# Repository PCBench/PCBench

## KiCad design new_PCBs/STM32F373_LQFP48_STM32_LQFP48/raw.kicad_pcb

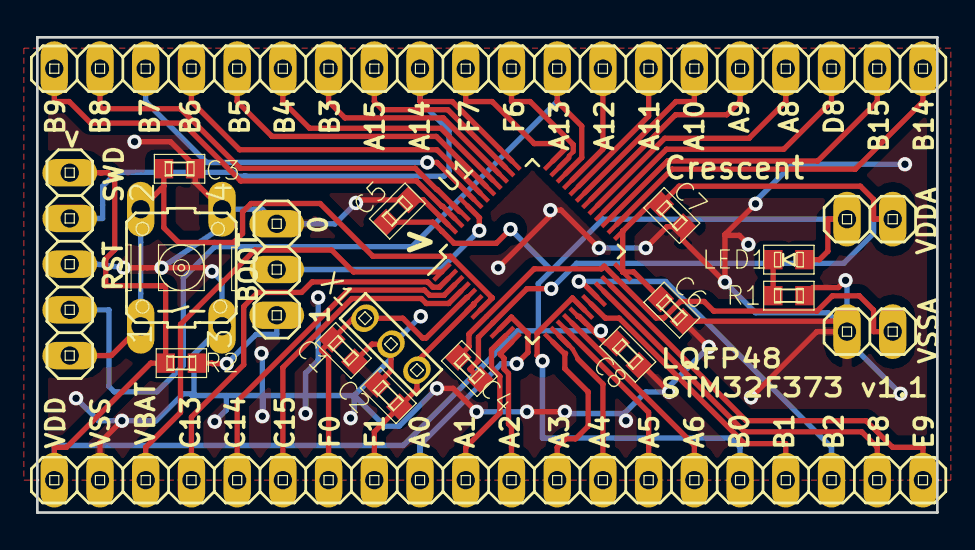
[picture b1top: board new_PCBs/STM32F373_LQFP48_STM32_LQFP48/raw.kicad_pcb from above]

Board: 2 copper layers, 50.0 x 26.4 mm, 20 parts (0 on the bottom side), 46 nets.

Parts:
C1, C2, C3, C4, C5, C6, C7, C8: CAPACITOR1608; generic-SMD1608
JP1: PINHD-1X5; pinhead-1X05
JP2: PINHD-1X3; pinhead-1X03
JP3, JP5: PINHD-1X2; pinhead-1X02
JP4, JP6: PINHD-1X20; pinhead-1X20
LED1: LED1608; generic-LED1608
R1, R2: RESISTOR1608; generic-SMD1608
S1: 10-XX; switch-omron-B3F-10XX
U1: STM32F100C8; LQFP-48_7x7mm_Pitch0.5mm
X1: CRYSTAL_SMD; pinhead-1X03

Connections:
BOOT: JP2.2, U1.44
NRST: C3.1, JP1.5, S1.1, S1.2, U1.7
unnamed: JP2.1, R2.2
unnamed: LED1.K, R1.1
OSCI: C1.1, JP4.7, U1.5, X1.1
OSCO: C2.1, JP4.8, U1.6, X1.2
PA0: JP4.9, U1.10
PA1: JP4.10, U1.11
PA2: JP4.11, U1.12
PA3: JP4.12, U1.13
PA4: JP4.13, U1.14
PA5: JP4.14, U1.15
PA6: JP4.15, U1.16
PA8: JP6.17, U1.29
PA9: JP6.16, U1.30
PA10: JP6.15, U1.31
PA11: JP6.14, U1.32
PA12: JP6.13, U1.33
PA13: JP1.4, JP6.12, U1.34
PA14: JP1.2, JP6.9, U1.37
PA15: JP6.8, U1.38
PB0: JP4.16, U1.18
PB1: JP4.17, U1.19
PB2: JP4.18, U1.20
PB3: JP6.7, U1.39
PB4: JP6.6, U1.40
PB5: JP6.5, U1.41
PB6: JP6.4, U1.42
PB7: JP6.3, U1.43
PB8: JP6.2, U1.45
PB9: JP6.1, U1.46
PB14: JP6.20, U1.26
PB15: JP6.19, U1.27
PC13: JP4.4, U1.2
PC14: JP4.5, U1.3
PC15: JP4.6, U1.4
PD8: JP6.18, U1.28
PE8: JP4.19, U1.21
PE9: JP4.20, U1.22
PF6: JP6.11, U1.35
PF7: JP6.10, U1.36
VBAT: JP4.3, U1.1
VDD: C5.1, C8.1, JP1.1, JP3.1, JP4.1, LED1.A, R2.1, U1.17, U1.48
VDDA: C4.1, C6.1, C7.1, JP3.2, U1.9, U1.24, U1.25
VSS: C1.2, C2.2, C3.2, C5.2, C6.2, C7.2, C8.2, JP1.3, JP2.3, JP4.2, JP5.1, R1.2, S1.3, S1.4, U1.47, X1.3
VSSA: C4.2, JP5.2, U1.8, U1.23

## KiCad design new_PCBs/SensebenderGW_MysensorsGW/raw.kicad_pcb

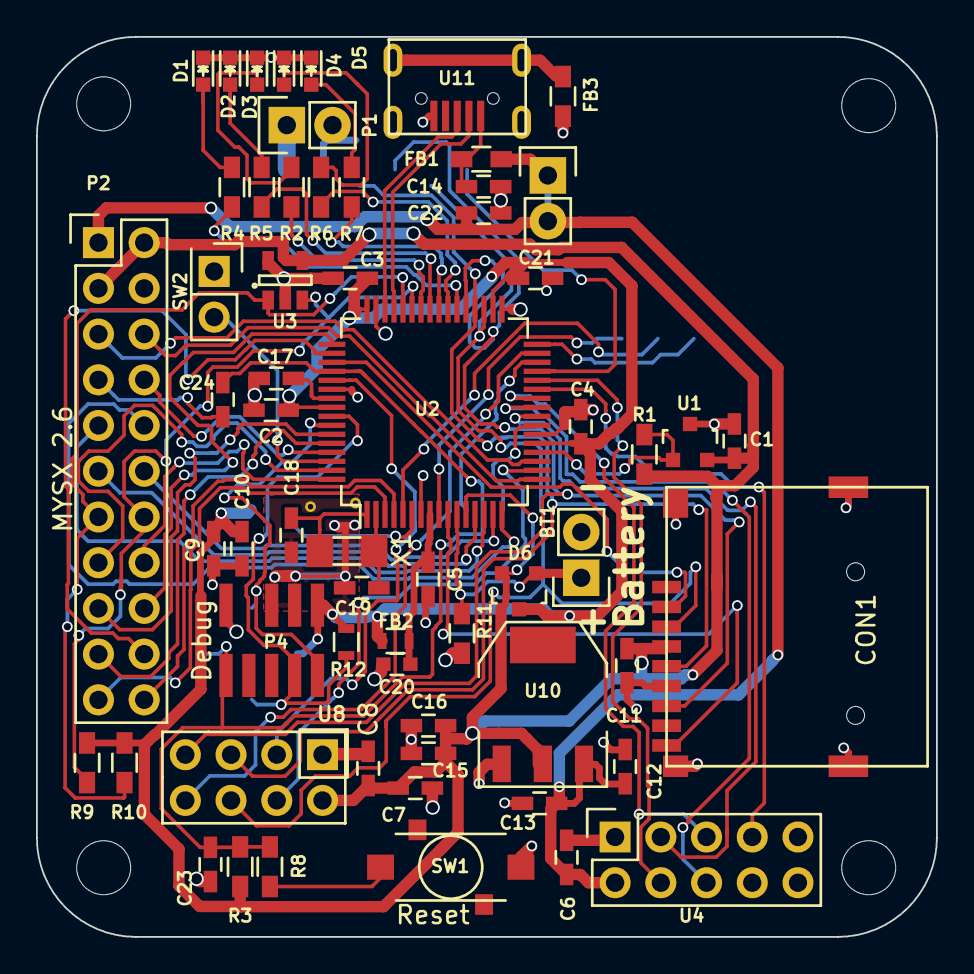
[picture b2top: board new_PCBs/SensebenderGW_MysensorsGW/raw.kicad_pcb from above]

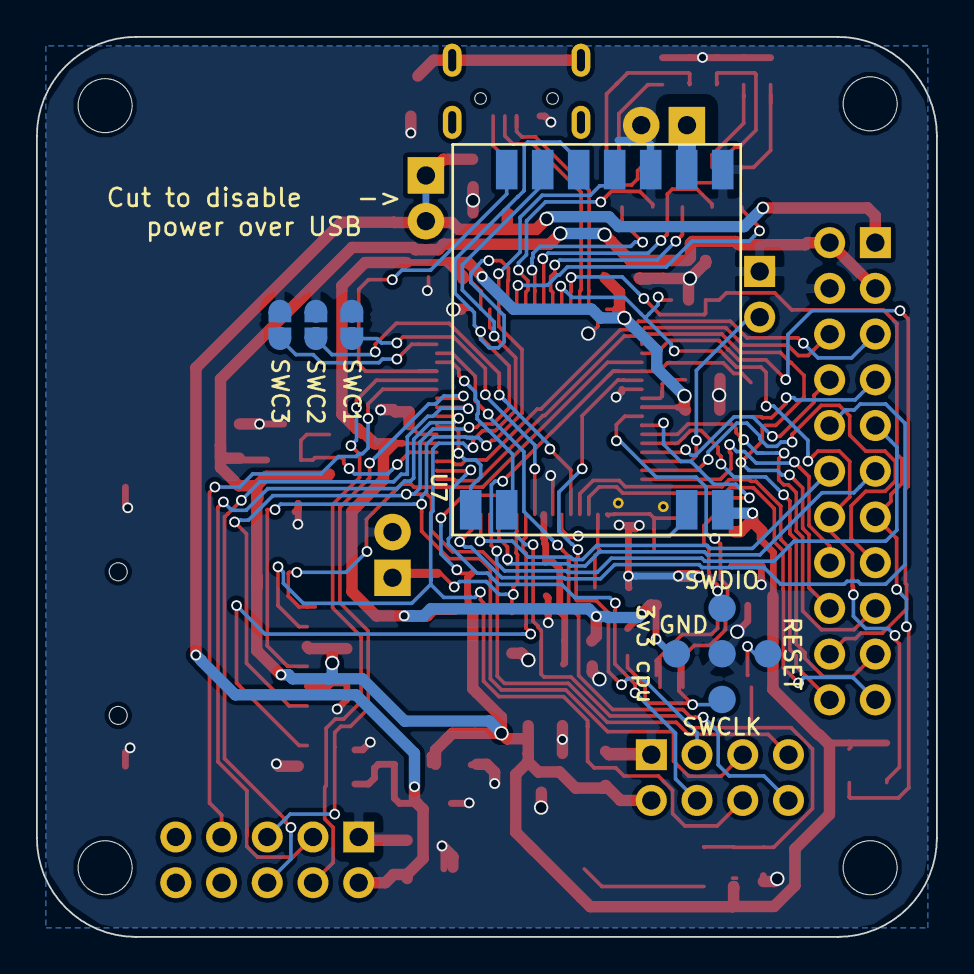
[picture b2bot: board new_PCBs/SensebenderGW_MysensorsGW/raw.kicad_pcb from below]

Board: 2 copper layers, 50.0 x 50.0 mm, 70 parts (9 on the bottom side), 68 nets.

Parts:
BT1: Battery; Pin_Header_Straight_1x02
C1, C2, C3, C4, C5, C6, C7, C10, C11, C13, C15, C17, C21, C24: 100nF; C_0603_HandSoldering
C8, C9, C12, C16: 10uF; C_0603_HandSoldering
C14, C22: 1nF; C_0603_HandSoldering
C18, C19: 4.7pF; C_0603_HandSoldering
C20: 10uF; C_0603
C23: 10nF; C_0603_HandSoldering
CON1: micro_SD_Card_SPI; MM027S020R
D1: LED_BLUE; LED-0603
D2: LED_RED; LED-0603
D3: LED_GREEN; LED-0603
D4: LED_YELLOW; LED-0603
D5: LED_ORANGE; LED-0603
D6: BAT54; SOT-23
FB1, FB3: 470R EMI; R_0603_HandSoldering
FB2: 470R EMI; R_0603
P1: ANT; Pin_Header_Straight_1x02
P2: MYSX 2.6; MYSX_2.6
P3: SWC3; 2_pin_solder_jumper_smd
P4: Debug; Cortex_M_Debug_Connector
P5: USB_PWR_DIS; Pin_Header_Straight_1x02
P6: SWC2; 2_pin_solder_jumper_smd
P7: SWC1; 2_pin_solder_jumper_smd
R1, R9, R10: 4k7; R_0603_HandSoldering
R2, R5, R6, R7: 270; R_0603_HandSoldering
R3: 100k; R_0603_HandSoldering
R4: 91; R_0603_HandSoldering
R8: 39R; R_0603_HandSoldering
R11: 1M; R_0603_HandSoldering
R12: 1K; R_0603
SW1: Reset; TS-021
SW2: SW_INCL; Pin_Header_Straight_2x01
U1: ATSHA204A; SOT-23
U2: ATSAMD21J; TQFP-64_10x10mm_Pitch0.5mm
U3: AT24CS32-STUM; SOT-23-5
U4: W5100
U7: RFM69HW; RFM69HW_SMD
U8: NRF24L01
U10: AMS1117-3.3; SOT-223
U11: MICRO-B_USB; Micro_USB
W1: SWDIO; Measurement_Point_Round-SMD-Pad_Small
W2: SWCLK; Measurement_Point_Round-SMD-Pad_Small
W3: RESET; Measurement_Point_Round-SMD-Pad_Small
W4: GND; Measurement_Point_Round-SMD-Pad_Small
W5: 3v3 cpu; Measurement_Point_Round-SMD-Pad_Small
X1: 32768hz; XTAL_3.2x1.5mm

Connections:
+3.3VP: C2.1, C3.1, C4.1, C21.1, D6.3, FB2.2, P4.1, R12.1, U2.21, U2.34, U2.48, U2.56, W5.1
+3V3: C1.1, C7.1, C8.1, C9.2, C10.2, C11.2, C15.1, C16.1, CON1.4, D6.2, P2.2, P2.3, R1.1, R3.1, R9.1, R10.1, U1.2, U2.12, U3.4, U7.8, U8.2, U10.2
+5V: C6.1, C12.1, C13.1, C22.1, FB1.1, P2.1, P5.1, P5.2, U4.2, U10.3
/A5: P2.21, U2.3
/A6: P2.22, U2.4
/BAT_DET: BT1.1, D6.1, R11.1, U2.11
/CE_NRF: U2.53, U8.3
/CS_NRF: U2.18, U8.4
/CS_RFM: U2.29, U7.15
/CS_SDCARD: CON1.2, U2.51
/D1_DFM: P2.5, U2.19
/D2_DTM: P2.6, U2.17
/D3_INT: P2.9, U2.14
/D4_INT: P2.10, U2.16
/D5_PWM: P2.11, U2.13
/D6_PWM: P2.12, U2.15
/D7_SCL: P2.13, R10.2, U2.44, U3.1
/D8_SDA: P2.14, R9.2, U2.43, U3.3
/D9_A3: P2.15, U2.63
/D10_A4: P2.16, U2.64
/D11_MOSI: P2.17, U2.59
/D12_MISO: P2.18, U2.49
/D13_SCK: P2.19, U2.60
/D14_CS: P2.20, U2.50
/D+: U2.46, U11.3
/D-: U2.45, U11.2
/INCL_SW: SW2.2, U2.62
/IRQ_NRF: U2.31, U8.8
/IRQ_RFM: U2.30, U7.2
/LED1: R4.2, U2.38
/LED2: R5.2, U2.41
/LED3: R2.2, U2.42
/LED4: R6.2, U2.39
/LED5: R7.2, U2.40
/LEGACY_ID: P2.8, U2.61
/MISO: CON1.7, U2.37, U7.13, U8.7
/MOSI: CON1.3, U2.35, U7.14, U8.6
/NET_MISO: U2.27, U4.7
/NET_MOSI: U2.25, U4.6
/NET_RST: U2.24, U4.3
/NET_SCK: U2.26, U4.5
/NET_SS: U2.28, U4.4
/RESET_RFM: U2.23, U7.1
/RFM_DIO5: U2.6, U7.7
/RST: C24.2, P2.7
/Reset: C23.1, C24.1, P4.10, R3.2, R8.1, U2.52, W3.1
/SCK: CON1.5, U2.36, U7.12, U8.5
/SDCARD_DET: CON1.9, U2.10
/SECURITY: R1.2, U1.1, U2.20
/SWC1: P7.2, U2.9
/SWC2: P6.1, U2.5
/SWC3: P3.2, U2.32
/SWCLK: P4.4, R12.2, U2.57, W2.1
/SWDIO: P4.2, U2.58, W1.1
GND: BT1.2, C1.2, C2.2, C3.2, C4.2, C5.2, C6.2, C7.2, C8.2, C9.1, C10.1, C11.1, C12.2, C13.2, C14.1, C15.2, C16.2, C17.1, C18.1, C19.1, C20.2, C21.2, C22.2, C23.2, CON1.6, CON1.10, D1.1, D2.1, D3.1, D4.1, D5.1, FB3.1, P1.2, P2.4, P3.1, P4.3, P4.5, P4.9, P6.2, P7.1, R11.2, SW1.1, SW2.1, U1.3, U2.7, U2.22, U2.33, U2.47, U2.54, U3.2, U3.5, U4.1, U7.9, U7.11, U8.1, U10.1, U11.5, W4.1
unnamed: C14.2, FB1.2, U11.1
unnamed: C17.2, U2.55
unnamed: C18.2, U2.1, X1.2
unnamed: C19.2, U2.2, X1.1
unnamed: C5.1, C20.1, FB2.1, U2.8
unnamed: D1.2, R4.1
unnamed: D2.2, R5.1
unnamed: D3.2, R2.1
unnamed: D4.2, R6.1
unnamed: D5.2, R7.1
unnamed: FB3.2, U11.6, U11.7
unnamed: P1.1, U7.10
unnamed: R8.2, SW1.2

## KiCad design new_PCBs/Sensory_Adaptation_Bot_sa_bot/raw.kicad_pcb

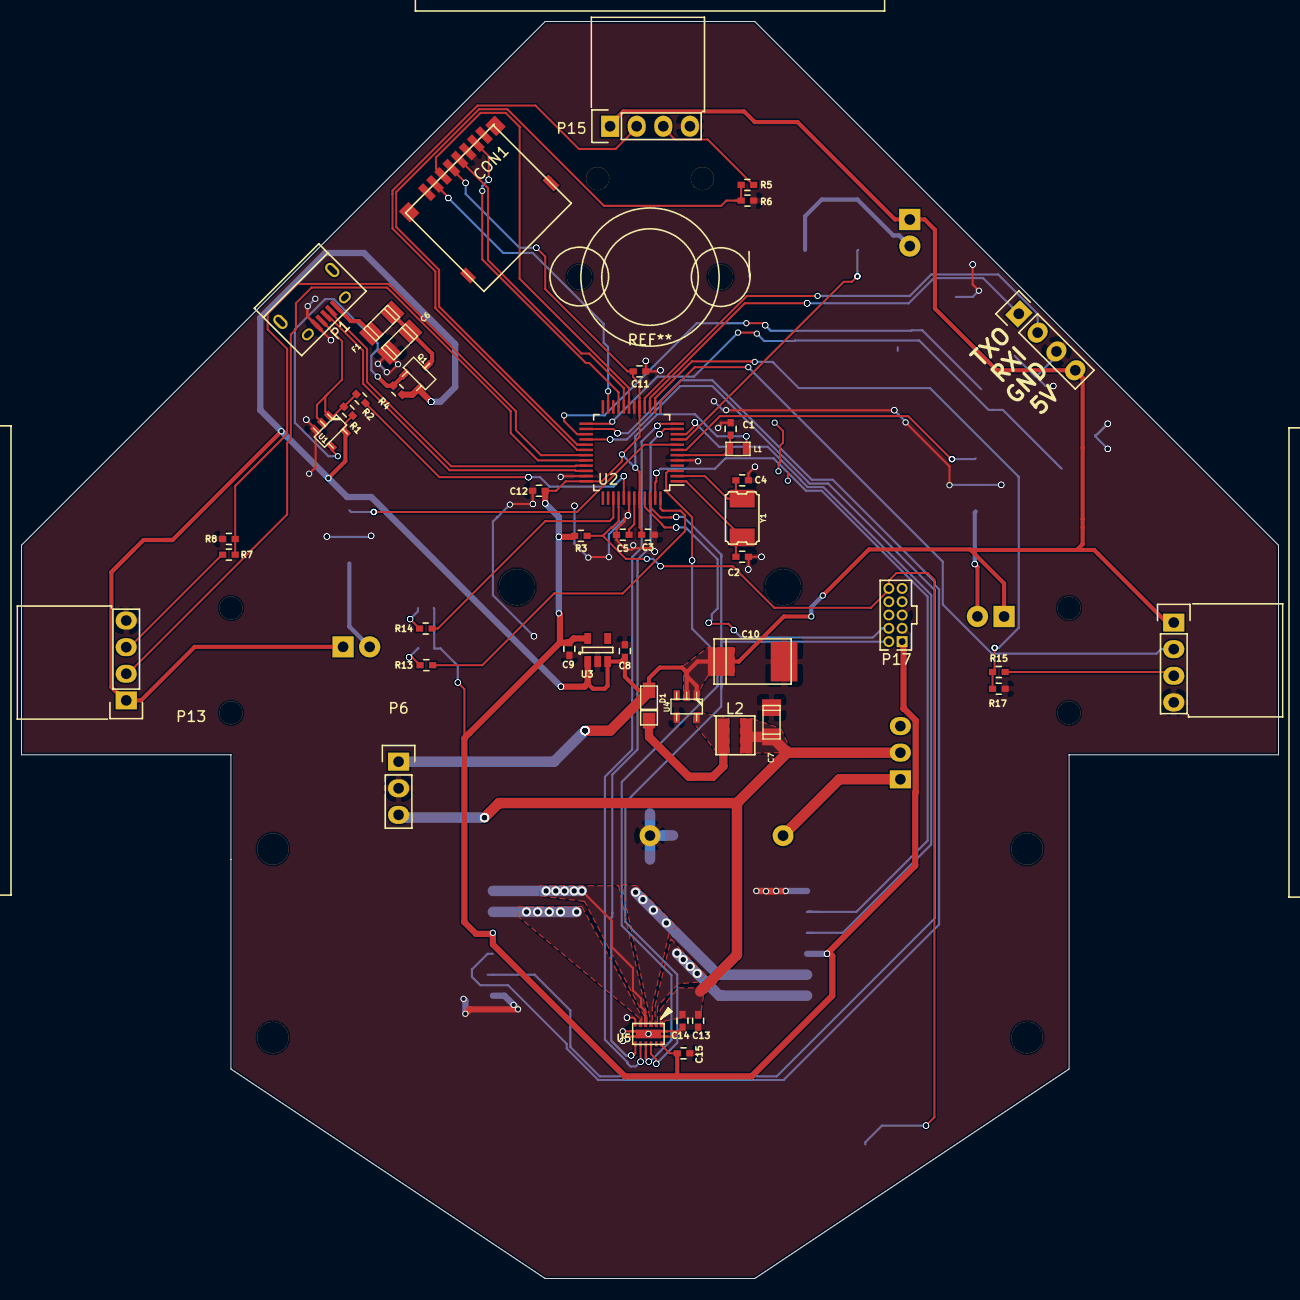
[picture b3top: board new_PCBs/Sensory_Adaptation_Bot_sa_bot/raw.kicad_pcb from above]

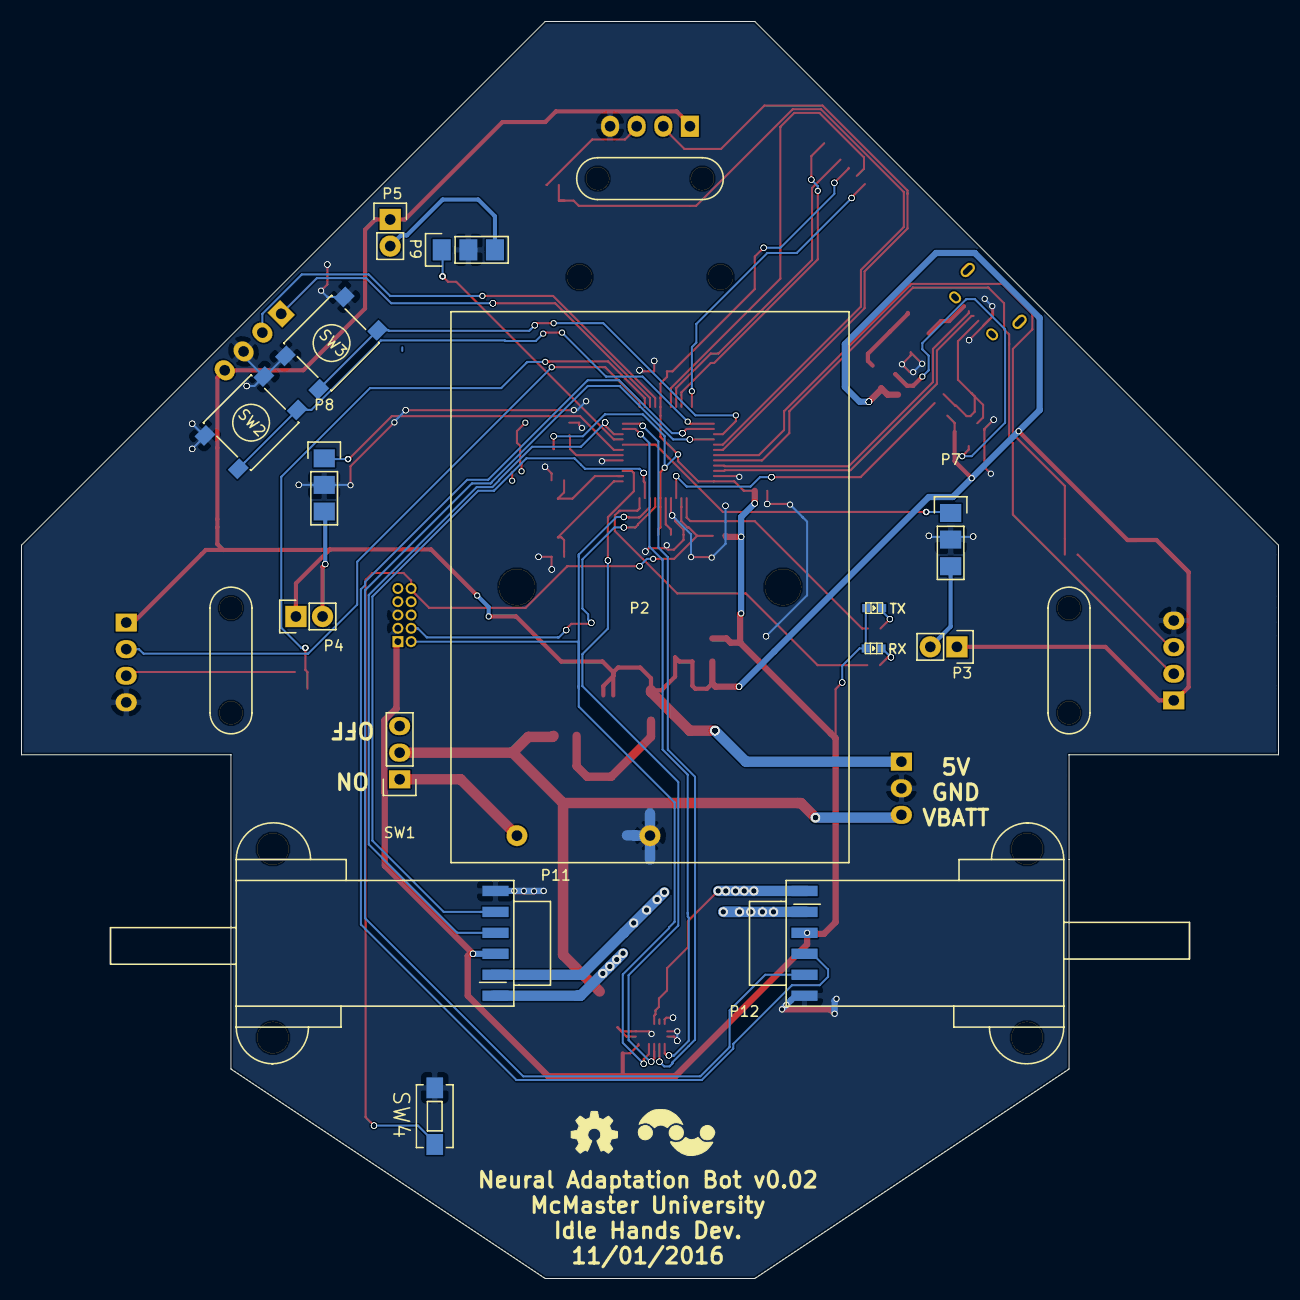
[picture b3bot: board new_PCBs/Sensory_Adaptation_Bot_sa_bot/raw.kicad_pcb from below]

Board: 2 copper layers, 120.0 x 120.0 mm, 61 parts (15 on the bottom side), 58 nets.

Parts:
C1, C3, C5, C11, C12, C14, C15: 0.1uF; C_0402_Hand
C2, C4: 15pF; C_0402_Hand
C6: 2.2uF; c_1206
C7: 10uF; c_1206
C8: 1uF; C_0402_Hand
C9: 2.2uF; C_0402_Hand
C10: 68uF; TantalC_SizeV_EIA-7343
C13: 10uF; C_0402_Hand
CON1: MicroSD_Card; MicroSD_Card_Receptacle
D1: BAT20J; sod323
D6: RX; Led_0603
D7: TX; Led_0603
F1: 500mA; c_1206
L1: FB - 30Ohm; R_SM0603
L2: 47uH; I_1212
P1: USB_OTG; USB_Micro-B
P2: BatteryHolder; Battery_3xAAA_Holder
P3: IR4_JMP; Pin_Header_Straight_1x02
P4: IR2_JMP; Pin_Header_Straight_1x02
P5: IR3_JMP; Pin_Header_Straight_1x02
P6: ExPower; Pin_Header_Straight_1x03
P7: IR_4; Pin_Header_SMD_1x03
P8: IR_2; Pin_Header_SMD_1x03
P9: IR_3; Pin_Header_SMD_1x03
P11: MOTOR_A; Motor_Pololu_Encoder
P12: MOTOR_B; Motor_Pololu_Encoder
P13: SONAR_4; SonarSensor_HCSR04
P14: SONAR_2; SonarSensor_HCSR04
P15: SONAR_3; SonarSensor_HCSR04
P17: DBG_CONN; Pin_Header_Straight_2x05_Pitch1.27mm
P18: CONN_01X04; Pin_Header_Straight_1x04
Q1: Q_PMOS_DSG; SOT23_DSG
R1: 100k; R_0402_Hand
R2: 330; R_0402_Hand
R3, R5, R6, R7, R8, R15, R17: 10k; R_0402_Hand
R4: 47K; R_0402_Hand
R13, R14: 1k; R_0402_Hand
SW1: SWITCH_INV; Pin_Header_Straight_1x03
SW2, SW3: SW_PUSH; SW_SPST_PTS645
SW4: SW_PUSH; SW_SPST_EVQPE1
U1: 74AHC1G125; sot23-5
U2: SAMD21G18; TQFP-48_7x7mm_Pitch0.5mm
U3: AP2112K-3.3V; SOT-23-5
U4: NCP1402; sot23-5
U5: DRV8835; WSON-12-2x3
Y1: Crystal_Small; crystal_smd_5x3.2mm

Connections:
+3V3: C3.1, C9.1, C11.1, C12.1, C15.1, CON1.4, D6.2, D7.2, L1.1, P11.3, P12.3, P17.1, R3.1, U2.17, U2.36, U2.44, U3.5, U5.12
/AENC1: P11.4, U2.10
/AENC2: P11.5, U2.47
/AIN2: U2.3, U5.9
/AM1: P11.1, U5.2
/AM2: P11.2, U5.3
/BENC1: P12.4, U2.26
/BENC2: P12.5, U2.28
/BIN1: U2.12, U5.8
/BIN2: U2.11, U5.7
/BM1: P12.1, U5.4
/BM2: P12.2, U5.5
/BUT1: SW2.1, U2.25
/BUT2: SW3.1, U2.27
/ECHO2: R15.1, R17.2, U2.14
/ECHO3: R5.1, R6.2, U2.29
/ECHO4: R7.1, R8.2, U2.31
/HVECHO2: P14.2, R15.2
/HVECHO3: P15.2, R5.2
/HVECHO4: P13.2, R7.2
/IR2: P8.1, U2.7
/IR3: P9.1, U2.9
/IR4: P7.1, U2.8
/RXI: P18.2, U2.16
/RXLED: R13.1, U2.48
/SD_CS: CON1.2, U2.23
/SPI_MISO: CON1.7, U2.21
/SPI_MOSI: CON1.3, U2.19
/SPI_SCK: CON1.5, U2.20
/TRIG2: P14.3, U2.13
/TRIG3: P15.3, U2.30
/TRIG4: P13.3, U2.32
/TXLED: R14.1, U2.39
/TXO: P18.1, U2.15
GND: C1.2, C2.2, C3.2, C4.2, C5.2, C6.2, C7.2, C8.2, C9.2, C10.2, C11.2, C12.2, C13.2, C14.2, C15.2, CON1.6, P1.5, P2.1, P6.2, P7.2, P8.2, P9.2, P11.6, P12.6, P13.1, P14.1, P15.1, P17.3, P17.5, P18.3, R6.1, R8.1, R17.1, SW2.2, SW3.2, SW4.2, U1.3, U2.5, U2.18, U2.35, U2.42, U3.2, U4.4, U5.6
unnamed: C1.1, L1.2, U2.6
unnamed: C2.1, U2.1, Y1.2
unnamed: C4.1, U2.2, Y1.1
unnamed: C5.1, U2.43
unnamed: D1.2, L2.2, U4.5
unnamed: D6.1, R13.2
unnamed: D7.1, R14.2
unnamed: F1.1, P1.1
unnamed: P3.2, P7.3
unnamed: P4.2, P8.3
unnamed: P5.2, P9.3
unnamed: Q1.3, R4.2, U1.4
RESET: P17.10, R3.2, SW4.1, U2.40
SBATT: C7.1, C13.1, C14.1, L2.1, P6.3, SW1.2, U5.1
SWCLK: P17.4, U2.45
SWDIO: P17.2, U2.46, U5.10
USB_D+: P1.3, U2.34
USB_D-: P1.2, U2.33
USB_HOST_EN: R2.2, U2.41
USB_ID: P1.4, R1.2, R2.1, U1.1, U1.2
VBATT: P2.2, SW1.1
VCC: C8.1, C10.1, D1.1, P3.1, P4.1, P5.1, P6.1, P13.4, P14.4, P15.4, P18.4, Q1.2, R1.1, R4.1, U1.5, U3.1, U3.3, U4.1, U4.2
VCOM: C6.1, F1.2, Q1.1

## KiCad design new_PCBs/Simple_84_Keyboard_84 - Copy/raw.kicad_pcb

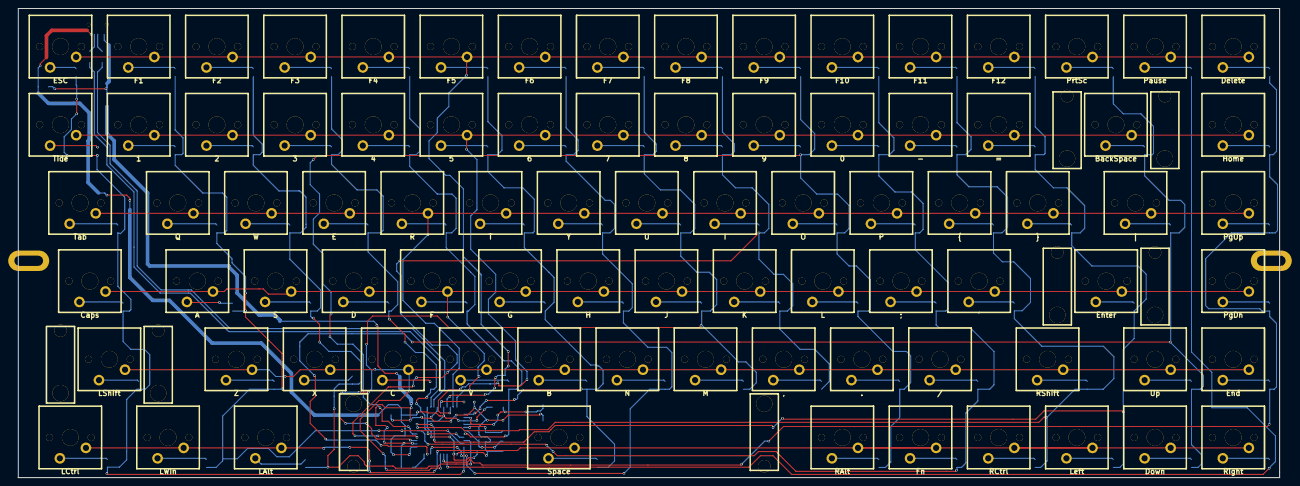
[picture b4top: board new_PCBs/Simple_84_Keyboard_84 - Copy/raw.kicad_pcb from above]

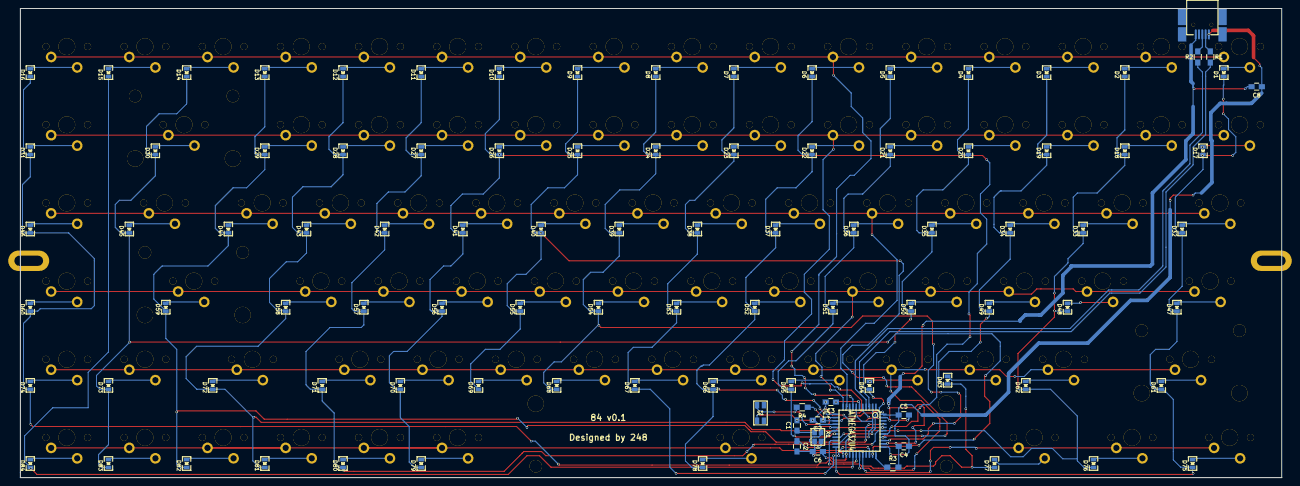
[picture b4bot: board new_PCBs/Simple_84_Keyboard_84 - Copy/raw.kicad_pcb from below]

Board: 2 copper layers, 307.3 x 114.3 mm, 194 parts (100 on the bottom side), 117 nets.

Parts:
C1, C2: 22pF; C_0805_HandSoldering
C3, C8: 1uF; C_0805_HandSoldering
C4, C5, C6, C7: 100nF; C_0805_HandSoldering
D1, D2, D3, D4, D5, D6, D7, D8, D9, D10, D11, D12, D13, D14, D15, D16, D17, D18, D19, D20, D21, D22, D23, D24, D25, D26, D27, D28, D29, D30, D31, D32, D33, D34, D35, D36, D37, D38, D39, D40, D41, D42, D43, D44, D45, D46, D47, D48, D49, D50, D51, D52, D53, D54, D55, D56, D57, D58, D59, D60, D61, D62, D63, D64, D65, D66, D67, D68, D69, D70, D71, D72, D73, D74, D75, D76, D77, D78, D79, D80, D81, D82, D83, D84: DIODE; SM0805D
IC1: ATMEGA32U4; TQFP44
J1: USBMINI_B05; 67503
MXLED: VAL**; PKRHSL
MXLED#2: VAL**; PKRHSL
MXST: VAL**; MXST
MXST#2, MXST#3, MXST#4, MXST#5, MXST#6, MXST#7, MXST#8: VAL**; MXST
R1, R2: 22R; R_0805_HandSoldering
R3, R4: 10K; R_0805_HandSoldering
S1: DTSM-6; TACT_4x3
S2: ESC; MX1A-simple
S3: F1; MX1A-simple
S4: F2; MX1A-simple
S5: F3; MX1A-simple
S6: F4; MX1A-simple
S7: F5; MX1A-simple
S8: F6; MX1A-simple
S9: F7; MX1A-simple
S10: F8; MX1A-simple
S11: F9; MX1A-simple
S12: F10; MX1A-simple
S13: F11; MX1A-simple
S14: F12; MX1A-simple
S15: PrtSc; MX1A-simple
S16: Pause; MX1A-simple
S17: Delete; MX1A-simple
S18: Tide; MX1A-simple
S19: 1; MX1A-simple
S20: 2; MX1A-simple
S21: 3; MX1A-simple
S22: 4; MX1A-simple
S23: 5; MX1A-simple
S24: 6; MX1A-simple
S25: 7; MX1A-simple
S26: 8; MX1A-simple
S27: 9; MX1A-simple
S28: 0; MX1A-simple
S29: -; MX1A-simple
S30: =; MX1A-simple
S31: BackSpace; MX1A-simple
S32: Home; MX1A-simple
S33: Tab; MX1A-simple
S34: Q; MX1A-simple
S35: W; MX1A-simple
S36: E; MX1A-simple
S37: R; MX1A-simple
S38: T; MX1A-simple
S39: Y; MX1A-simple
S40: U; MX1A-simple
S41: I; MX1A-simple
S42: O; MX1A-simple
S43: P; MX1A-simple
S44: {; MX1A-simple
S45: }; MX1A-simple
S46: |; MX1A-simple
S47: PgUp; MX1A-simple
S48: Caps; MX1A-simple
S49: A; MX1A-simple
S50: S; MX1A-simple
S51: D; MX1A-simple
S52: F; MX1A-simple
S53: G; MX1A-simple
S54: H; MX1A-simple
S55: J; MX1A-simple
S56: K; MX1A-simple
S57: L; MX1A-simple
S58: ;; MX1A-simple
S59: '; MX1A-simple
S60: Enter; MX1A-simple
S61: PgDn; MX1A-simple
S62: LShift; MX1A-simple
S63: Z; MX1A-simple
S64: X; MX1A-simple
S65: C; MX1A-simple
S66: V; MX1A-simple
S67: B; MX1A-simple
S68: N; MX1A-simple
S69: M; MX1A-simple
S70: ,; MX1A-simple
S71: .; MX1A-simple
S72: /; MX1A-simple
S73: RShift; MX1A-simple
S74: Up; MX1A-simple
S75: End; MX1A-simple
S76: LCtrl; MX1A-simple
S77: LWin; MX1A-simple
S78: LAlt; MX1A-simple
S79: Space; MX1A-simple
S80: RAlt; MX1A-simple
S81: Fn; MX1A-simple
S82: RCtrl; MX1A-simple
S83: Left; MX1A-simple
S84: Down; MX1A-simple
S85: Right; MX1A-simple
X1: ASX4; ASX3F

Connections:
/switch_matrix/Col1: D1.2, D17.2, D32.2, D47.2, D61.2, D75.2, IC1.22
/switch_matrix/Col2: D2.2, D18.2, D33.2, D48.2, D62.2, D76.2, IC1.21
/switch_matrix/Col3: D3.2, D19.2, D34.2, D49.2, D63.2, D77.2, IC1.20
/switch_matrix/Col4: D4.2, D20.2, D35.2, D50.2, D64.2, IC1.19
/switch_matrix/Col5: D5.2, D21.2, D36.2, D51.2, D65.2, IC1.18
/switch_matrix/Col6: D6.2, D22.2, D37.2, D52.2, D66.2, D78.2, IC1.12
/switch_matrix/Col7: D7.2, D23.2, D38.2, D53.2, D67.2, IC1.31
/switch_matrix/Col8: D8.2, D24.2, D39.2, D54.2, D68.2, IC1.36
/switch_matrix/Col9: D9.2, D25.2, D40.2, D55.2, D69.2, IC1.37
/switch_matrix/Col10: D10.2, D26.2, D41.2, D56.2, D70.2, D79.2, IC1.38
/switch_matrix/Col11: D11.2, D27.2, D42.2, D57.2, D71.2, D80.2, IC1.39
/switch_matrix/Col12: D12.2, D28.2, D43.2, D58.2, D72.2, D81.2, IC1.40
/switch_matrix/Col13: D13.2, D29.2, D44.2, D59.2, D82.2, IC1.41
/switch_matrix/Col14: D14.2, D30.2, D45.2, D73.2, D83.2, IC1.32
/switch_matrix/Col15: D15.2, D84.2, IC1.26
/switch_matrix/Col16: D16.2, D31.2, D46.2, D60.2, D74.2, IC1.27
/switch_matrix/Row1: IC1.8, S2.1, S3.1, S4.1, S5.1, S6.1, S7.1, S8.1, S9.1, S10.1, S11.1, S12.1, S13.1, S14.1, S15.1, S16.1, S17.1
/switch_matrix/Row2: IC1.9, S18.1, S19.1, S20.1, S21.1, S22.1, S23.1, S24.1, S25.1, S26.1, S27.1, S28.1, S29.1, S30.1, S31.1, S32.1
/switch_matrix/Row3: IC1.10, S33.1, S34.1, S35.1, S36.1, S37.1, S38.1, S39.1, S40.1, S41.1, S42.1, S43.1, S44.1, S45.1, S46.1, S47.1
/switch_matrix/Row4: IC1.11, S48.1, S49.1, S50.1, S51.1, S52.1, S53.1, S54.1, S55.1, S56.1, S57.1, S58.1, S59.1, S60.1, S61.1
/switch_matrix/Row5: IC1.28, S62.1, S63.1, S64.1, S65.1, S66.1, S67.1, S68.1, S69.1, S70.1, S71.1, S72.1, S73.1, S74.1, S75.1
/switch_matrix/Row6: IC1.29, S76.1, S77.1, S78.1, S79.1, S80.1, S81.1, S82.1, S83.1, S84.1, S85.1
GND: C1.2, C2.2, C3.2, C4.2, C5.2, C6.2, C7.2, C8.2, IC1.5, IC1.15, IC1.23, IC1.35, IC1.43, J1.5, R3.2, S1.1, X1.2, X1.4
unnamed: C1.1, IC1.16, X1.1
unnamed: C2.1, IC1.17, X1.3
unnamed: C3.1, IC1.6
unnamed: D1.1, S2.2
unnamed: D2.1, S3.2
unnamed: D3.1, S4.2
unnamed: D4.1, S5.2
unnamed: D5.1, S6.2
unnamed: D6.1, S7.2
unnamed: D7.1, S8.2
unnamed: D8.1, S9.2
unnamed: D9.1, S10.2
unnamed: D10.1, S11.2
unnamed: D11.1, S12.2
unnamed: D12.1, S13.2
unnamed: D13.1, S14.2
unnamed: D14.1, S15.2
unnamed: D15.1, S16.2
unnamed: D16.1, S17.2
unnamed: D17.1, S18.2
unnamed: D18.1, S19.2
unnamed: D19.1, S20.2
unnamed: D20.1, S21.2
unnamed: D21.1, S22.2
unnamed: D22.1, S23.2
unnamed: D23.1, S24.2
unnamed: D24.1, S25.2
unnamed: D25.1, S26.2
unnamed: D26.1, S27.2
unnamed: D27.1, S28.2
unnamed: D28.1, S29.2
unnamed: D29.1, S30.2
unnamed: D30.1, S31.2
unnamed: D31.1, S32.2
unnamed: D32.1, S33.2
unnamed: D33.1, S34.2
unnamed: D34.1, S35.2
unnamed: D35.1, S36.2
unnamed: D36.1, S37.2
unnamed: D37.1, S38.2
unnamed: D38.1, S39.2
unnamed: D39.1, S40.2
unnamed: D40.1, S41.2
unnamed: D41.1, S42.2
unnamed: D42.1, S43.2
unnamed: D43.1, S44.2
unnamed: D44.1, S45.2
unnamed: D45.1, S46.2
unnamed: D46.1, S47.2
unnamed: D47.1, S48.2
unnamed: D48.1, S49.2
unnamed: D49.1, S50.2
unnamed: D50.1, S51.2
unnamed: D51.1, S52.2
unnamed: D52.1, S53.2
unnamed: D53.1, S54.2
unnamed: D54.1, S55.2
unnamed: D55.1, S56.2
unnamed: D56.1, S57.2
unnamed: D57.1, S58.2
unnamed: D58.1, S59.2
unnamed: D59.1, S60.2
unnamed: D60.1, S61.2
unnamed: D61.1, S62.2
unnamed: D62.1, S63.2
unnamed: D63.1, S64.2
unnamed: D64.1, S65.2
unnamed: D65.1, S66.2
unnamed: D66.1, S67.2
unnamed: D67.1, S68.2
unnamed: D68.1, S69.2
unnamed: D69.1, S70.2
unnamed: D70.1, S71.2
unnamed: D71.1, S72.2
unnamed: D72.1, S73.2
unnamed: D73.1, S74.2
unnamed: D74.1, S75.2
unnamed: D75.1, S76.2
unnamed: D76.1, S77.2
unnamed: D77.1, S78.2
unnamed: D78.1, S79.2
unnamed: D79.1, S80.2
unnamed: D80.1, S81.2
unnamed: D81.1, S82.2
unnamed: D82.1, S83.2
unnamed: D83.1, S84.2
unnamed: D84.1, S85.2
unnamed: IC1.3, R1.2
unnamed: IC1.4, R2.1
unnamed: IC1.13, R4.2, S1.3
unnamed: IC1.33, R3.1
unnamed: J1.2, R1.1
unnamed: J1.3, R2.2
VCC: C4.1, C5.1, C6.1, C7.1, C8.1, IC1.2, IC1.7, IC1.14, IC1.24, IC1.34, IC1.44, J1.1, R4.1

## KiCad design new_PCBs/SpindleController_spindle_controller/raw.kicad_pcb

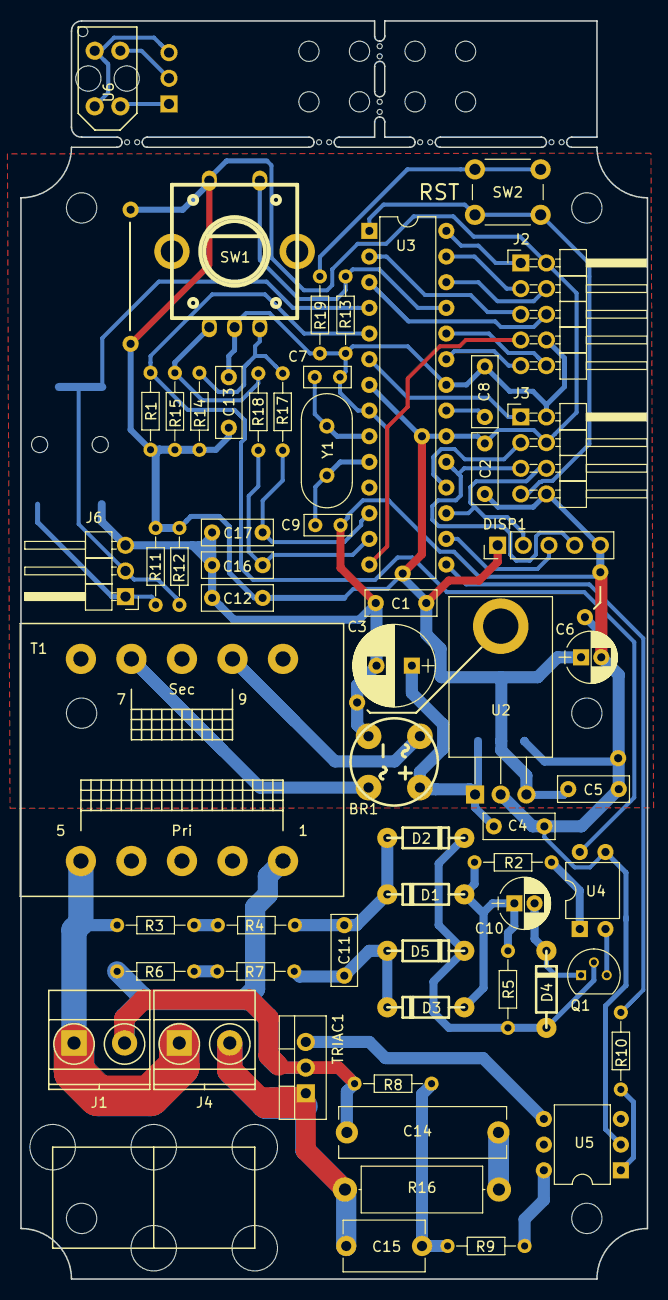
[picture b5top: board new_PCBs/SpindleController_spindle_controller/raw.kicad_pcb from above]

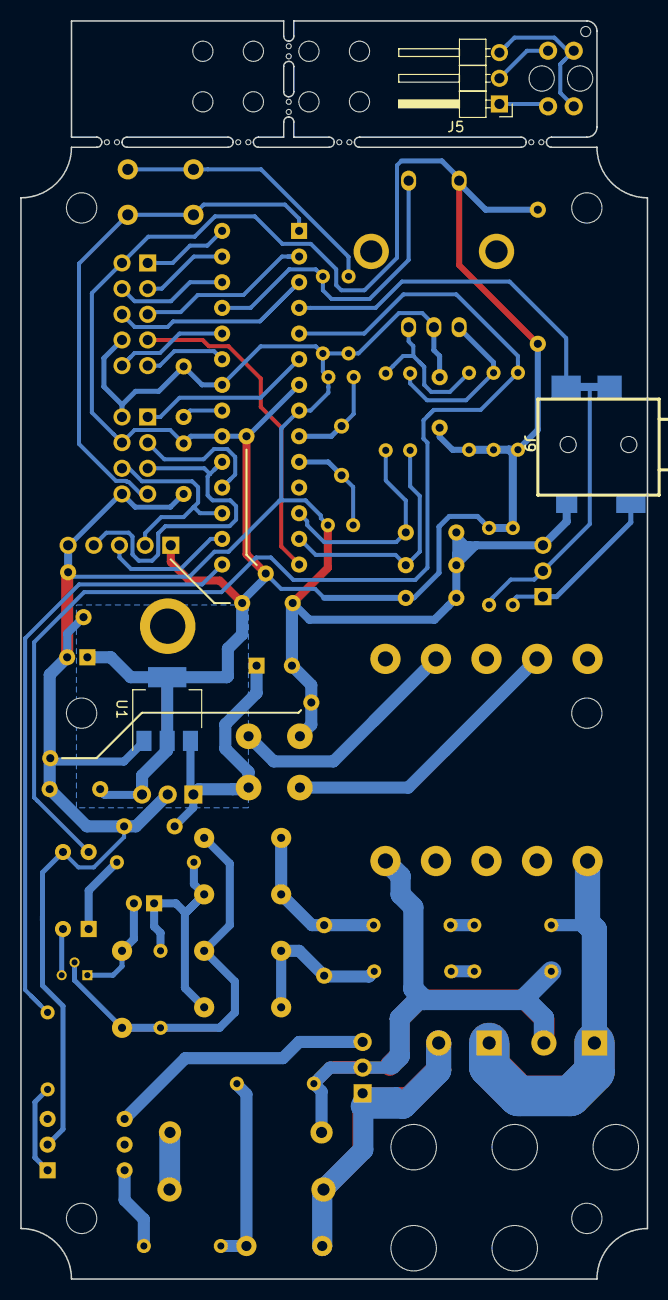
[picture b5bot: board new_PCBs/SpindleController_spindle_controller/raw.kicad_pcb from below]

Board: 2 copper layers, 62.0 x 124.5 mm, 72 parts (3 on the bottom side), 52 nets.

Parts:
BR1: D_Bridge_+AA-; bridge_wob
C1, C2, C5, C8, C12, C13: 100n; C_Rect_L7.0mm_W2.5mm_P5.00mm
C3: 220u; CP_Radial_D8.0mm_P3.50mm
C4: 470n; C_Rect_L7.0mm_W2.5mm_P5.00mm
C6: 100u; CP_Radial_D5.0mm_P2.00mm
C7, C9: 27p; C_Rect_L4.6mm_W2.0mm_P2.50mm_MKS02_FKP02
C10: 10u; CP_Radial_D5.0mm_P2.00mm
C11: 1n; C_Rect_L7.0mm_W2.5mm_P5.00mm
C14: 10n; C_Rect_L16.5mm_W5.0mm_P15.00mm_MKT
C15: 1n; C_Disc_D8.0mm_W5.0mm_P7.50mm
C16, C17: 47n; C_Rect_L7.0mm_W2.5mm_P5.00mm
CASE1: Case; CASE_KEMO_G085N+BREAKAWAY_SENSOR
D1, D2, D3, D4, D5: 1N4841; diode_do35
DISP1: 8x7SEG; Pin_Header_Straight_1x05_Pitch2.54mm
J1: VAC 230V; TerminalBlock_Pheonix_MKDS1.5-2pol
J2: AUX/CONTROL; Pin_Header_Angled_2x05_Pitch2.54mm
J3: ICP; Pin_Header_Angled_2x04_Pitch2.54mm
J4: Load output; TerminalBlock_Pheonix_MKDS1.5-2pol
J5, J6: CONN_01X03; Pin_Header_Angled_1x03_Pitch2.54mm
J7, J7#2, J7#3, J7#4: GND_JUMPER; JUMPER_PIN
J8, J8#2, J8#3, J8#4: VCC_JUMPER; JUMPER_PIN
J9: Jack_3.5mm_4pin; jack_3.5_sj1-3514-smt
Q1: 2N3904; TO-92_Molded_Narrow
R1, R12, R13, R14, R15: 10k; R_Axial_DIN0204_L3.6mm_D1.6mm_P7.62mm_Horizontal
R2, R10: 1k; R_Axial_DIN0204_L3.6mm_D1.6mm_P7.62mm_Horizontal
R3, R6: 120k; R_Axial_DIN0204_L3.6mm_D1.6mm_P7.62mm_Horizontal
R4, R7: 220k; R_Axial_DIN0204_L3.6mm_D1.6mm_P7.62mm_Horizontal
R5: 33k; R_Axial_DIN0204_L3.6mm_D1.6mm_P7.62mm_Horizontal
R8: 470; R_Axial_DIN0204_L3.6mm_D1.6mm_P7.62mm_Horizontal
R9, R19: 360; R_Axial_DIN0204_L3.6mm_D1.6mm_P7.62mm_Horizontal
R11: 220; R_Axial_DIN0204_L3.6mm_D1.6mm_P7.62mm_Horizontal
R16: 47; R_Axial_DIN0414_L11.9mm_D4.5mm_P15.24mm_Horizontal
R17, R18: 2k2; R_Axial_DIN0204_L3.6mm_D1.6mm_P7.62mm_Horizontal
SW1: Rotary_Encoder_Switch; encoder_alps-ec12d
SW2: SW_SPST; SW_PUSH_6mm
T1: 230 - 6VAC (Spitznagel SPK 01406); Trafo_CHK-EI30-2VA_1xSec
TRIAC1: BT138; TO-220_Vertical
U1: LT1117-5; SOT-223
U2: LM2940CT-5.0; TO-220_Horizontal_connected_tab
U3: ATMEGA328P-PU; DIP-28_W7.62mm
U4: PC817; DIP-4_W7.62mm
U5: MOC3020M; DIP-6_W7.62mm
U6: TCRT5000
WIRESTRAP1: 2x Ziplock wire strap; WireStrap_2X_5HOLES
Y1: 16MHz; Crystal_HC49-U_Vertical

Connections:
/DBG: J3.1, U3.6
/MISO: J3.3, U3.18
/MOSI: DISP1.2, J3.6, U3.17
/PB0: J2.7, U3.14
/PC3: J2.4, U3.26
/PD6: J2.9, U3.23
/PD7: J2.10, U3.24
/RENC_A: C16.2, R18.2, U3.13
/RENC_B: C17.2, R17.2, U3.12
/ROT_PULSE: J6.2, J9.2, J9.3, R12.1, U3.4
/RST: J3.7, SW2.1, U3.1
/RX: J2.5, U3.2
/SCK: DISP1.4, J3.5, U3.19
/SCL: J2.1, U3.28
/SDA: J2.3, U3.27
/SEG_CS: DISP1.3, U3.16
/SW1: R13.2, SW1.4, U3.25
/TRIAC_DRIVE: R10.1, U3.15
/TX: J2.6, U3.3
/VAC_L: C14.1, J1.2, R6.2, R8.2, T1.1, TRIAC1.2
/VAC_N: J1.1, J4.1, R3.2, T1.5
/ZCROSS_PULSE: R1.1, U3.5, U4.4
GND: BR1.4, C1.2, C2.1, C3.2, C4.2, C5.2, C6.2, C7.2, C8.2, C9.2, C12.2, C13.1, C16.1, C17.1, DISP1.5, J2.8, J3.2, J3.8, J6.3, J7.1, J7#2.1, J7#3.1, J7#4.1, J9.4, R13.1, R19.2, SW1.2, U1.1, U2.2, U3.8, U3.22, U4.3, U5.2
unnamed: BR1.1, C3.1, C4.1, U1.3, U2.1
unnamed: BR1.2, T1.9
unnamed: BR1.3, T1.7
unnamed: C7.1, U3.9, Y1.1
unnamed: C8.1, U3.21
unnamed: C9.1, U3.10, Y1.2
unnamed: C10.1, D1.1, D3.1, R2.2, R5.2
unnamed: C10.2, D4.2, Q1.1
unnamed: C11.1, D1.2, D2.1, R4.1
unnamed: C11.2, D3.2, D5.1, R7.1
unnamed: C14.2, R16.2
unnamed: C15.1, R8.1, R9.2
unnamed: C15.2, J4.2, R16.1, TRIAC1.1
unnamed: D2.2, D4.1, D5.2, Q1.2, R5.1
unnamed: J5.1, U6.1
unnamed: J5.2, U6.4
unnamed: J5.3, U6.2, U6.3
unnamed: J6.1, J9.1, R11.2
unnamed: Q1.3, U4.2
unnamed: R2.1, U4.1
unnamed: R3.1, R4.2
unnamed: R6.1, R7.2
unnamed: R9.1, U5.6
unnamed: R10.2, U5.1
unnamed: R14.1, R17.1, SW1.3
unnamed: R15.1, R18.1, SW1.1
unnamed: R19.1, SW2.2
unnamed: TRIAC1.3, U5.4
VCC: C1.1, C2.2, C5.1, C6.1, C12.1, C13.2, DISP1.1, J2.2, J3.4, J8.1, J8#2.1, J8#3.1, J8#4.1, R1.2, R11.1, R12.2, R14.2, R15.2, SW1.5, U1.2, U1.4, U2.3, U3.7, U3.20
